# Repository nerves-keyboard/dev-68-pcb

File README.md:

# Dev-68

A 68-key development keyboard designed for working on the [Xebow](https://github.com/ElixirSeattle/xebow) firmware.

- [Bill of materials](https://docs.google.com/spreadsheets/d/1IPxDRe5p0AkolHPQgk4m-Z4O2ABlp4nutEiS4CgZYm4/edit?usp=sharing)

- [Layout](http://www.keyboard-layout-editor.com/##@@=~%0AEsc&=!%0A1&=%22%0A2&=%23%0A3&=$%0A4&=%25%0A5&=%5E%0A6&=%2F&%0A7&=*%0A8&=(%0A9&=)%0A0&=%2F_%0A-&=+%0A%2F=&_w:2%3B&=Backspace&_x:0.25%3B&=Ins&=Pg%20Up%3B&@_w:1.5%3B&=Tab&=Q&=W&=E&=R&=T&=Y&=U&=I&=O&=P&=%7B%0A%5B&=%7D%0A%5D&_w:1.5%3B&=%7C%0A%5C&_x:0.25%3B&=Del&=Pg%20Dn%3B&@_w:1.75%3B&=Caps%20Lock&=A&=S&=D&=F&=G&=H&=J&=K&=L&=%2F:%0A%2F%3B&=%22%0A'&_w:2.25%3B&=Enter%3B&@_w:2.25%3B&=Shift&=Z&=X&=C&=V&=B&=N&=M&=%3C%0A,&=%3E%0A.&=%3F%0A%2F%2F&_w:2.75%3B&=Shift&_x:0.25%3B&=%E2%86%91%3B&@_w:1.25%3B&=Ctrl&_w:1.25%3B&=Super&_w:1.25%3B&=Alt&_w:6.25%3B&=&_w:1.25%3B&=Fn&_w:1.25%3B&=Alt&_w:1.25%3B&=Ctrl&_x:0.5%3B&=%E2%86%90&=%E2%86%93&=%E2%86%92)

- PCB

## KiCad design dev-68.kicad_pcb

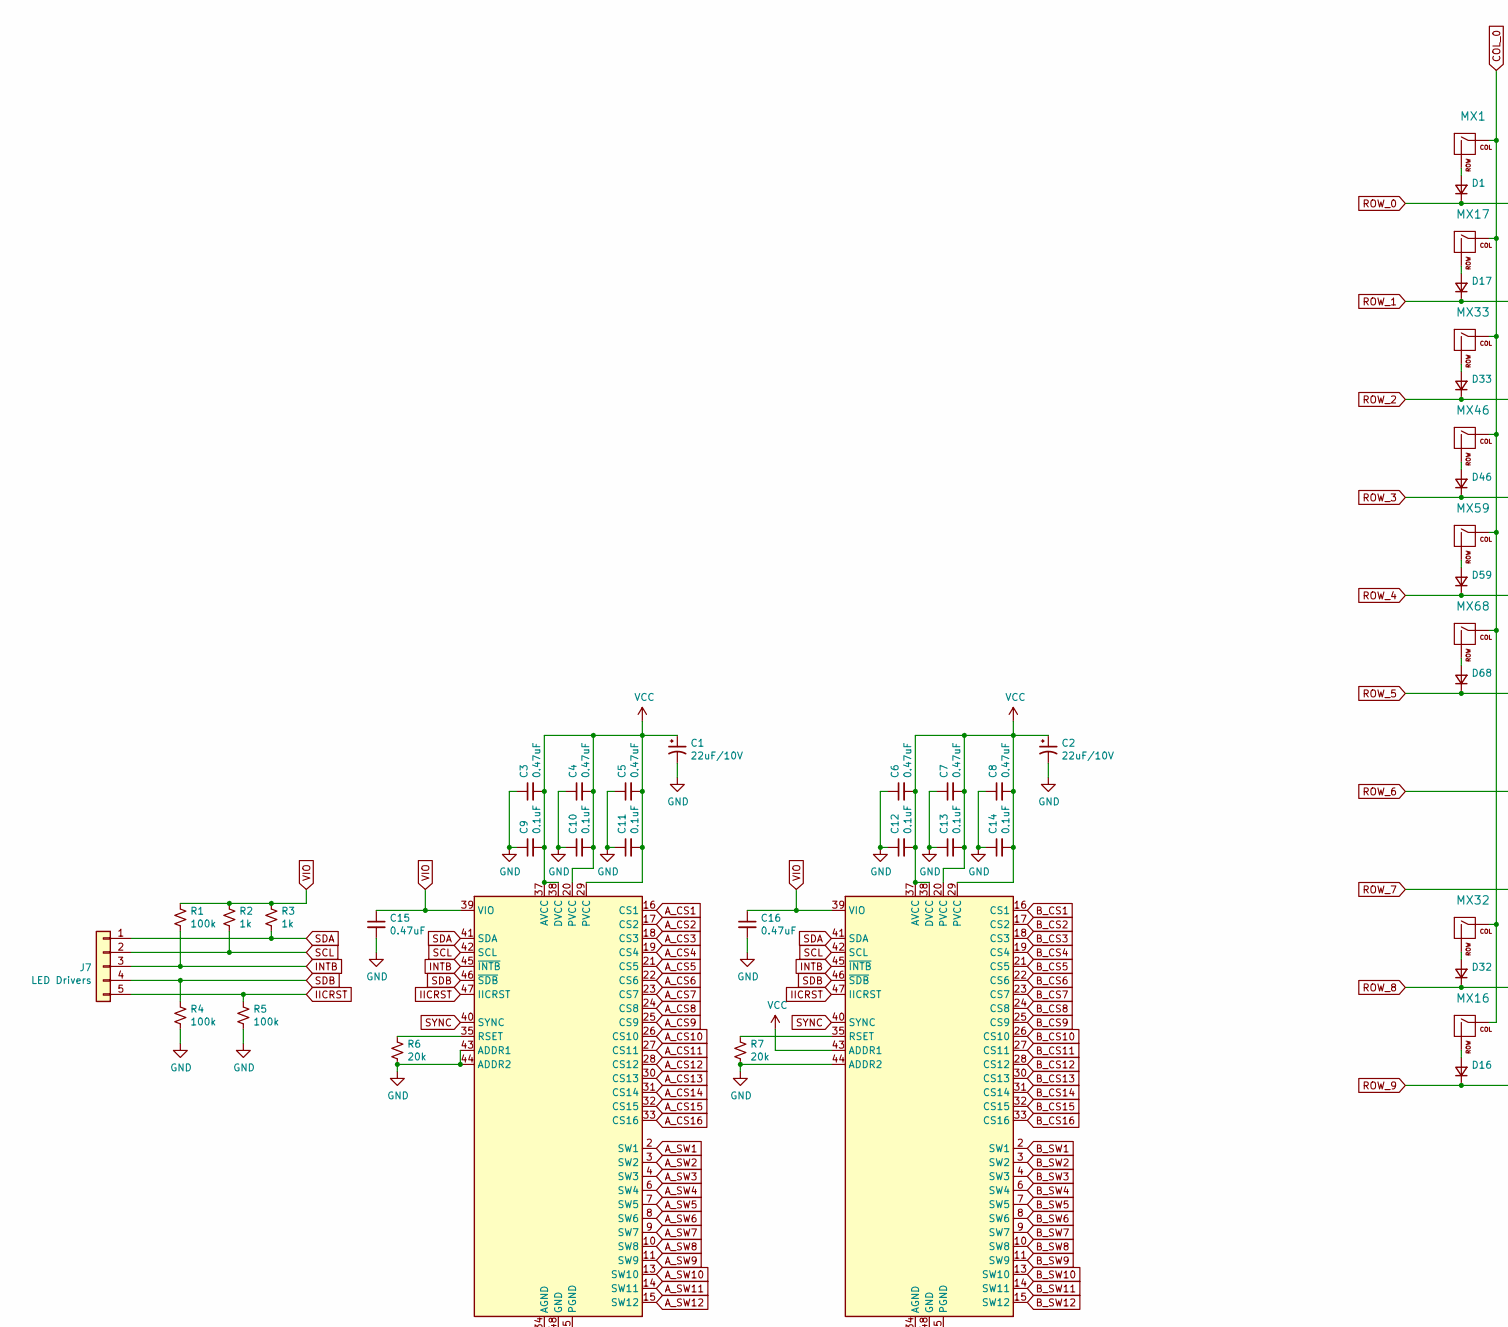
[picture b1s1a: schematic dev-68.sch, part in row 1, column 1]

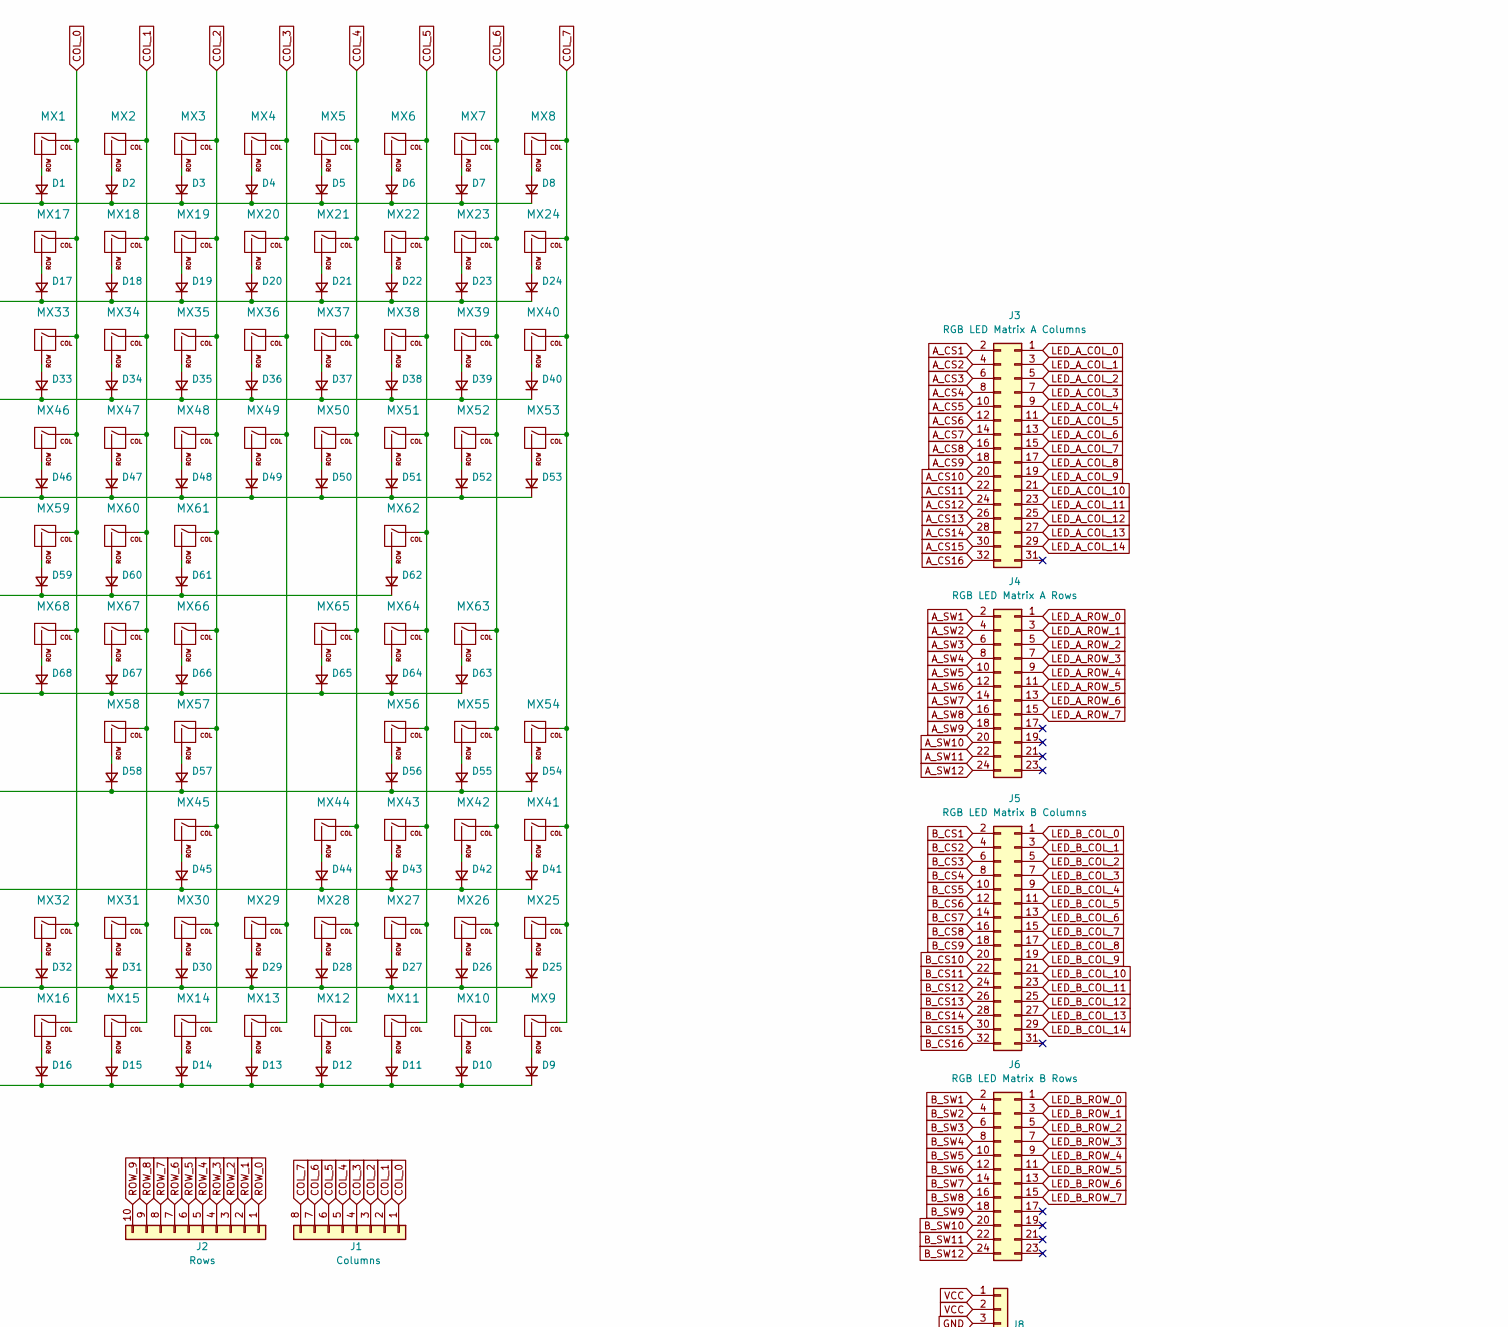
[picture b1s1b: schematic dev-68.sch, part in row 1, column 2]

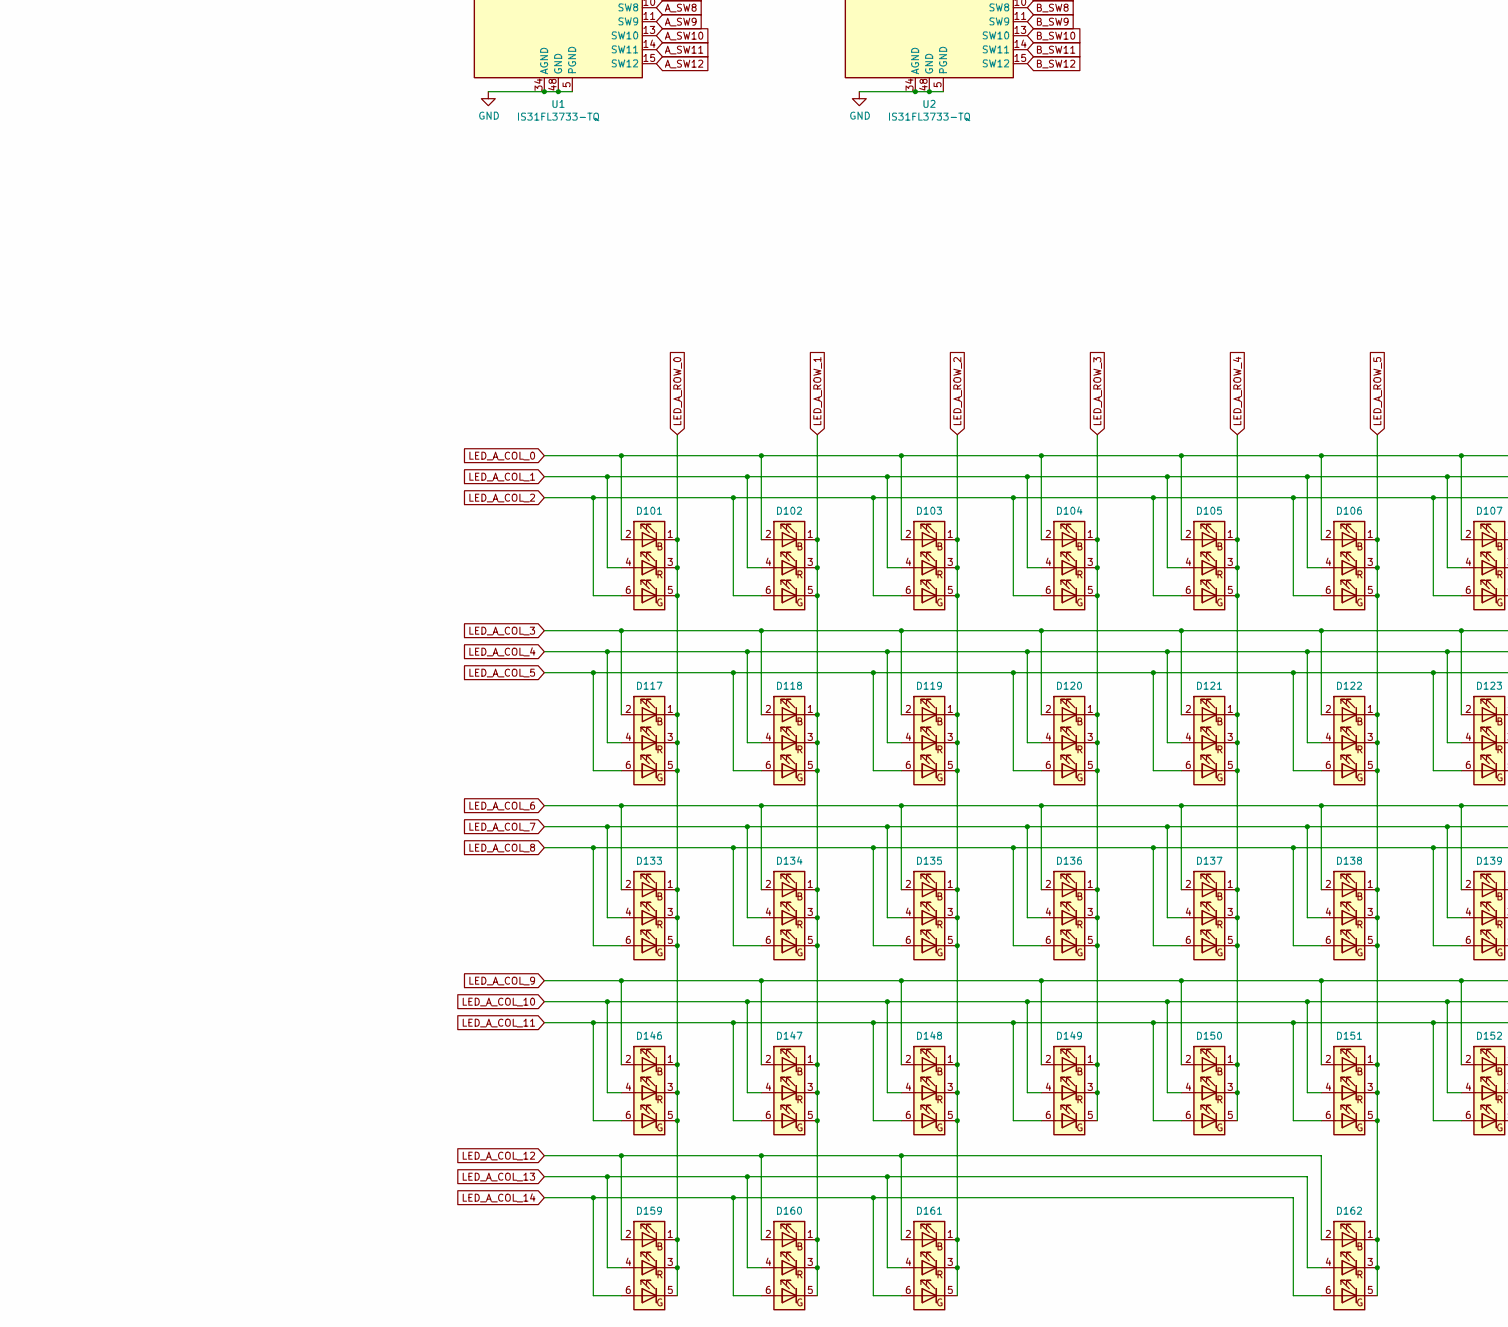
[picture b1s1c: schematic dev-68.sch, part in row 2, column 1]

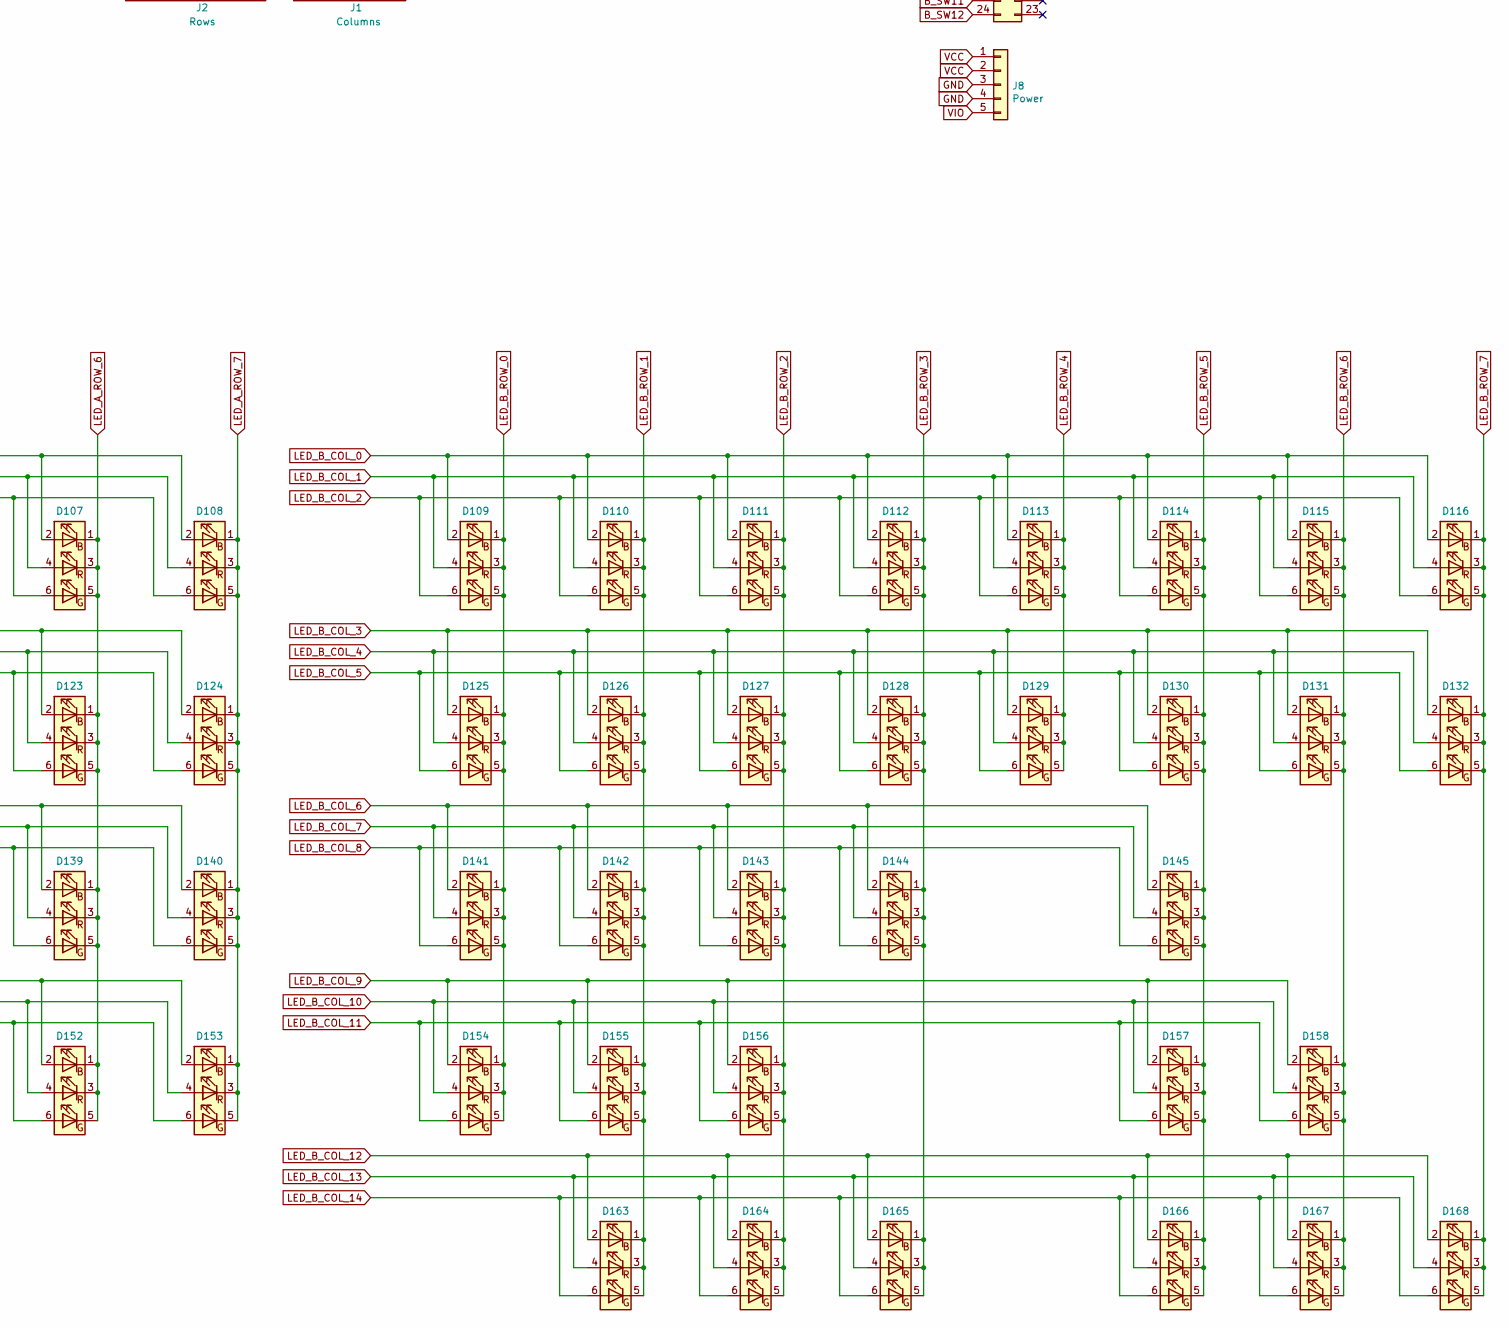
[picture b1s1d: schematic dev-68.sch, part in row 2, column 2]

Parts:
C1, C2: 22uF/10V; CP_Radial_D4.0mm_P1.50mm
C3, C4, C5, C6, C7, C8, C15, C16: 0.47uF; C_1206_3216Metric_Pad1.42x1.75mm_HandSolder
C9, C10, C11, C12, C13, C14: 0.1uF; C_1206_3216Metric_Pad1.42x1.75mm_HandSolder
D1, D2, D3, D4, D5, D6, D7, D8, D9, D10, D11, D12, D13, D14, D15, D16, D17, D18, D19, D20, D21, D22, D23, D24, D25, D26, D27, D28, D29, D30, D31, D32, D33, D34, D35, D36, D37, D38, D39, D40, D41, D42, D43, D44, D45, D46, D47, D48, D49, D50, D51, D52, D53, D54, D55, D56, D57, D58, D59, D60, D61, D62, D63, D64, D65, D66, D67, D68: D_small; D_1206_3216Metric_Pad1.42x1.75mm_HandSolder
D101, D102, D103, D104, D105, D106, D107, D108, D109, D110, D111, D112, D113, D114, D115, D116, D117, D118, D119, D120, D121, D122, D123, D124, D125, D126, D127, D128, D129, D130, D131, D132, D133, D134, D135, D136, D137, D138, D139, D140, D141, D142, D143, D144, D145, D146, D147, D148, D149, D150, D151, D152, D153, D154, D155, D156, D157, D158, D159, D160, D161, D162, D163, D164, D165, D166, D167, D168: LED_RGB; Wurth_PLCC6
J1: Columns; PinHeader_1x08_P2.54mm_Vertical
J2: Rows; PinHeader_1x10_P2.54mm_Vertical
J3: RGB LED Matrix A Columns; PinHeader_2x16_P2.54mm_Vertical
J4: RGB LED Matrix A Rows; PinHeader_2x12_P2.54mm_Vertical
J5: RGB LED Matrix B Columns; PinHeader_2x16_P2.54mm_Vertical
J6: RGB LED Matrix B Rows; PinHeader_2x12_P2.54mm_Vertical
J7: LED Drivers; PinHeader_1x05_P2.54mm_Vertical
J8: Power; PinHeader_1x05_P2.54mm_Vertical
MX1, MX2, MX3, MX4, MX5, MX6, MX7, MX8, MX9, MX10, MX11, MX12, MX13, MX15, MX16, MX18, MX19, MX20, MX21, MX22, MX23, MX24, MX25, MX26, MX27, MX28, MX29, MX31, MX32, MX34, MX35, MX36, MX37, MX38, MX39, MX40, MX41, MX42, MX43, MX44, MX47, MX48, MX49, MX50, MX51, MX52, MX53, MX54, MX55, MX56, MX58, MX66, MX67, MX68: MX-NoLED; MXOnly-1U-Hotswap
MX14: MX-NoLED; MXOnly-2U-Hotswap-ReversedStabilizers
MX17, MX30: MX-NoLED; MXOnly-1.5U-Hotswap
MX33: MX-NoLED; MXOnly-1.75U-Hotswap
MX45, MX46: MX-NoLED; MXOnly-2.25U-Hotswap-ReversedStabilizers
MX57: MX-NoLED; MXOnly-2.75U-Hotswap-ReversedStabilizers
MX59, MX60, MX61, MX63, MX64, MX65: MX-NoLED; MXOnly-1.25U-Hotswap
MX62: MX-NoLED; MXOnly-6.25U-Hotswap-ReversedStabilizers
R1, R4, R5: 100k; R_1206_3216Metric_Pad1.42x1.75mm_HandSolder
R2, R3: 1k; R_1206_3216Metric_Pad1.42x1.75mm_HandSolder
R6, R7: 20k; R_1206_3216Metric_Pad1.42x1.75mm_HandSolder
U1, U2: IS31FL3733-TQ; TQFP-48-1EP_7x7mm_P0.5mm_EP5x5mm

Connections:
A_CS1: J3.2, U1.16 (CS1)
A_CS2: J3.4, U1.17 (CS2)
A_CS3: J3.6, U1.18 (CS3)
A_CS4: J3.8, U1.19 (CS4)
A_CS5: J3.10, U1.21 (CS5)
A_CS6: J3.12, U1.22 (CS6)
A_CS7: J3.14, U1.23 (CS7)
A_CS8: J3.16, U1.24 (CS8)
A_CS9: J3.18, U1.25 (CS9)
A_CS10: J3.20, U1.26 (CS10)
A_CS11: J3.22, U1.27 (CS11)
A_CS12: J3.24, U1.28 (CS12)
A_CS13: J3.26, U1.30 (CS13)
A_CS14: J3.28, U1.31 (CS14)
A_CS15: J3.30, U1.32 (CS15)
A_CS16: J3.32, U1.33 (CS16)
A_SW1: J4.2, U1.2 (SW1)
A_SW2: J4.4, U1.3 (SW2)
A_SW3: J4.6, U1.4 (SW3)
A_SW4: J4.8, U1.6 (SW4)
A_SW5: J4.10, U1.7 (SW5)
A_SW6: J4.12, U1.8 (SW6)
A_SW7: J4.14, U1.9 (SW7)
A_SW8: J4.16, U1.10 (SW8)
A_SW9: J4.18, U1.11 (SW9)
A_SW10: J4.20, U1.13 (SW10)
A_SW11: J4.22, U1.14 (SW11)
A_SW12: J4.24, U1.15 (SW12)
B_CS1: J5.2, U2.16 (CS1)
B_CS2: J5.4, U2.17 (CS2)
B_CS3: J5.6, U2.18 (CS3)
B_CS4: J5.8, U2.19 (CS4)
B_CS5: J5.10, U2.21 (CS5)
B_CS6: J5.12, U2.22 (CS6)
B_CS7: J5.14, U2.23 (CS7)
B_CS8: J5.16, U2.24 (CS8)
B_CS9: J5.18, U2.25 (CS9)
B_CS10: J5.20, U2.26 (CS10)
B_CS11: J5.22, U2.27 (CS11)
B_CS12: J5.24, U2.28 (CS12)
B_CS13: J5.26, U2.30 (CS13)
B_CS14: J5.28, U2.31 (CS14)
B_CS15: J5.30, U2.32 (CS15)
B_CS16: J5.32, U2.33 (CS16)
B_SW1: J6.2, U2.2 (SW1)
B_SW2: J6.4, U2.3 (SW2)
B_SW3: J6.6, U2.4 (SW3)
B_SW4: J6.8, U2.6 (SW4)
B_SW5: J6.10, U2.7 (SW5)
B_SW6: J6.12, U2.8 (SW6)
B_SW7: J6.14, U2.9 (SW7)
B_SW8: J6.16, U2.10 (SW8)
B_SW9: J6.18, U2.11 (SW9)
B_SW10: J6.20, U2.13 (SW10)
B_SW11: J6.22, U2.14 (SW11)
B_SW12: J6.24, U2.15 (SW12)
COL_0: J1.1, MX1.1 (COL), MX16.1 (COL), MX17.1 (COL), MX32.1 (COL), MX33.1 (COL), MX46.1 (COL), MX59.1 (COL), MX68.1 (COL)
COL_1: J1.2, MX2.1 (COL), MX15.1 (COL), MX18.1 (COL), MX31.1 (COL), MX34.1 (COL), MX47.1 (COL), MX58.1 (COL), MX60.1 (COL), MX67.1 (COL)
COL_2: J1.3, MX3.1 (COL), MX14.1 (COL), MX19.1 (COL), MX30.1 (COL), MX35.1 (COL), MX45.1 (COL), MX48.1 (COL), MX57.1 (COL), MX61.1 (COL), MX66.1 (COL)
COL_3: J1.4, MX4.1 (COL), MX13.1 (COL), MX20.1 (COL), MX29.1 (COL), MX36.1 (COL), MX49.1 (COL)
COL_4: J1.5, MX5.1 (COL), MX12.1 (COL), MX21.1 (COL), MX28.1 (COL), MX37.1 (COL), MX44.1 (COL), MX50.1 (COL), MX65.1 (COL)
COL_5: J1.6, MX6.1 (COL), MX11.1 (COL), MX22.1 (COL), MX27.1 (COL), MX38.1 (COL), MX43.1 (COL), MX51.1 (COL), MX56.1 (COL), MX62.1 (COL), MX64.1 (COL)
COL_6: J1.7, MX7.1 (COL), MX10.1 (COL), MX23.1 (COL), MX26.1 (COL), MX39.1 (COL), MX42.1 (COL), MX52.1 (COL), MX55.1 (COL), MX63.1 (COL)
COL_7: J1.8, MX8.1 (COL), MX9.1 (COL), MX24.1 (COL), MX25.1 (COL), MX40.1 (COL), MX41.1 (COL), MX53.1 (COL), MX54.1 (COL)
GND: C1.2, C2.2, C3.1, C4.1, C5.1, C6.1, C7.1, C8.1, C9.1, C10.1, C11.1, C12.1, C13.1, C14.1, C15.2, C16.2, J8.3, J8.4, R4.2, R5.2, R6.2, R7.2, U1.5 (PGND), U1.12 (PGND), U1.34 (AGND), U1.43 (ADDR1), U1.44 (ADDR2), U1.48 (GND), U1.49 (GND), U2.5 (PGND), U2.12 (PGND), U2.34 (AGND), U2.44 (ADDR2), U2.48 (GND), U2.49 (GND)
IICRST: J7.5, R5.1, U1.47 (IICRST), U2.47 (IICRST)
INTB: J7.3, R1.2, U1.45 (~INTB), U2.45 (~INTB)
LED_A_COL_0: D101.2 (BA), D102.2 (BA), D103.2 (BA), D104.2 (BA), D105.2 (BA), D106.2 (BA), D107.2 (BA), D108.2 (BA), J3.1
LED_A_COL_1: D101.4 (RA), D102.4 (RA), D103.4 (RA), D104.4 (RA), D105.4 (RA), D106.4 (RA), D107.4 (RA), D108.4 (RA), J3.3
LED_A_COL_2: D101.6 (GA), D102.6 (GA), D103.6 (GA), D104.6 (GA), D105.6 (GA), D106.6 (GA), D107.6 (GA), D108.6 (GA), J3.5
LED_A_COL_3: D117.2 (BA), D118.2 (BA), D119.2 (BA), D120.2 (BA), D121.2 (BA), D122.2 (BA), D123.2 (BA), D124.2 (BA), J3.7
LED_A_COL_4: D117.4 (RA), D118.4 (RA), D119.4 (RA), D120.4 (RA), D121.4 (RA), D122.4 (RA), D123.4 (RA), D124.4 (RA), J3.9
LED_A_COL_5: D117.6 (GA), D118.6 (GA), D119.6 (GA), D120.6 (GA), D121.6 (GA), D122.6 (GA), D123.6 (GA), D124.6 (GA), J3.11
LED_A_COL_6: D133.2 (BA), D134.2 (BA), D135.2 (BA), D136.2 (BA), D137.2 (BA), D138.2 (BA), D139.2 (BA), D140.2 (BA), J3.13
LED_A_COL_7: D133.4 (RA), D134.4 (RA), D135.4 (RA), D136.4 (RA), D137.4 (RA), D138.4 (RA), D139.4 (RA), D140.4 (RA), J3.15
LED_A_COL_8: D133.6 (GA), D134.6 (GA), D135.6 (GA), D136.6 (GA), D137.6 (GA), D138.6 (GA), D139.6 (GA), D140.6 (GA), J3.17
LED_A_COL_9: D146.2 (BA), D147.2 (BA), D148.2 (BA), D149.2 (BA), D150.2 (BA), D151.2 (BA), D152.2 (BA), D153.2 (BA), J3.19
LED_A_COL_10: D146.4 (RA), D147.4 (RA), D148.4 (RA), D149.4 (RA), D150.4 (RA), D151.4 (RA), D152.4 (RA), D153.4 (RA), J3.21
LED_A_COL_11: D146.6 (GA), D147.6 (GA), D148.6 (GA), D149.6 (GA), D150.6 (GA), D151.6 (GA), D152.6 (GA), D153.6 (GA), J3.23
LED_A_COL_12: D159.2 (BA), D160.2 (BA), D161.2 (BA), D162.2 (BA), J3.25
LED_A_COL_13: D159.4 (RA), D160.4 (RA), D161.4 (RA), D162.4 (RA), J3.27
LED_A_COL_14: D159.6 (GA), D160.6 (GA), D161.6 (GA), D162.6 (GA), J3.29
LED_A_ROW_0: D101.1 (BK), D101.3 (RK), D101.5 (GK), D117.1 (BK), D117.3 (RK), D117.5 (GK), D133.1 (BK), D133.3 (RK), D133.5 (GK), D146.1 (BK), D146.3 (RK), D146.5 (GK), D159.1 (BK), D159.3 (RK), D159.5 (GK), J4.1
LED_A_ROW_1: D102.1 (BK), D102.3 (RK), D102.5 (GK), D118.1 (BK), D118.3 (RK), D118.5 (GK), D134.1 (BK), D134.3 (RK), D134.5 (GK), D147.1 (BK), D147.3 (RK), D147.5 (GK), D160.1 (BK), D160.3 (RK), D160.5 (GK), J4.3
LED_A_ROW_2: D103.1 (BK), D103.3 (RK), D103.5 (GK), D119.1 (BK), D119.3 (RK), D119.5 (GK), D135.1 (BK), D135.3 (RK), D135.5 (GK), D148.1 (BK), D148.3 (RK), D148.5 (GK), D161.1 (BK), D161.3 (RK), D161.5 (GK), J4.5
LED_A_ROW_3: D104.1 (BK), D104.3 (RK), D104.5 (GK), D120.1 (BK), D120.3 (RK), D120.5 (GK), D136.1 (BK), D136.3 (RK), D136.5 (GK), D149.1 (BK), D149.3 (RK), D149.5 (GK), J4.7
LED_A_ROW_4: D105.1 (BK), D105.3 (RK), D105.5 (GK), D121.1 (BK), D121.3 (RK), D121.5 (GK), D137.1 (BK), D137.3 (RK), D137.5 (GK), D150.1 (BK), D150.3 (RK), D150.5 (GK), J4.9
LED_A_ROW_5: D106.1 (BK), D106.3 (RK), D106.5 (GK), D122.1 (BK), D122.3 (RK), D122.5 (GK), D138.1 (BK), D138.3 (RK), D138.5 (GK), D151.1 (BK), D151.3 (RK), D151.5 (GK), D162.1 (BK), D162.3 (RK), D162.5 (GK), J4.11
LED_A_ROW_6: D107.1 (BK), D107.3 (RK), D107.5 (GK), D123.1 (BK), D123.3 (RK), D123.5 (GK), D139.1 (BK), D139.3 (RK), D139.5 (GK), D152.1 (BK), D152.3 (RK), D152.5 (GK), J4.13
LED_A_ROW_7: D108.1 (BK), D108.3 (RK), D108.5 (GK), D124.1 (BK), D124.3 (RK), D124.5 (GK), D140.1 (BK), D140.3 (RK), D140.5 (GK), D153.1 (BK), D153.3 (RK), D153.5 (GK), J4.15
LED_B_COL_0: D109.2 (BA), D110.2 (BA), D111.2 (BA), D112.2 (BA), D113.2 (BA), D114.2 (BA), D115.2 (BA), D116.2 (BA), J5.1
LED_B_COL_1: D109.4 (RA), D110.4 (RA), D111.4 (RA), D112.4 (RA), D113.4 (RA), D114.4 (RA), D115.4 (RA), D116.4 (RA), J5.3
LED_B_COL_2: D109.6 (GA), D110.6 (GA), D111.6 (GA), D112.6 (GA), D113.6 (GA), D114.6 (GA), D115.6 (GA), D116.6 (GA), J5.5
LED_B_COL_3: D125.2 (BA), D126.2 (BA), D127.2 (BA), D128.2 (BA), D129.2 (BA), D130.2 (BA), D131.2 (BA), D132.2 (BA), J5.7
LED_B_COL_4: D125.4 (RA), D126.4 (RA), D127.4 (RA), D128.4 (RA), D129.4 (RA), D130.4 (RA), D131.4 (RA), D132.4 (RA), J5.9
LED_B_COL_5: D125.6 (GA), D126.6 (GA), D127.6 (GA), D128.6 (GA), D129.6 (GA), D130.6 (GA), D131.6 (GA), D132.6 (GA), J5.11
LED_B_COL_6: D141.2 (BA), D142.2 (BA), D143.2 (BA), D144.2 (BA), D145.2 (BA), J5.13
LED_B_COL_7: D141.4 (RA), D142.4 (RA), D143.4 (RA), D144.4 (RA), D145.4 (RA), J5.15
LED_B_COL_8: D141.6 (GA), D142.6 (GA), D143.6 (GA), D144.6 (GA), D145.6 (GA), J5.17
LED_B_COL_9: D154.2 (BA), D155.2 (BA), D156.2 (BA), D157.2 (BA), D158.2 (BA), J5.19
LED_B_COL_10: D154.4 (RA), D155.4 (RA), D156.4 (RA), D157.4 (RA), D158.4 (RA), J5.21
LED_B_COL_11: D154.6 (GA), D155.6 (GA), D156.6 (GA), D157.6 (GA), D158.6 (GA), J5.23
LED_B_COL_12: D163.2 (BA), D164.2 (BA), D165.2 (BA), D166.2 (BA), D167.2 (BA), D168.2 (BA), J5.25
LED_B_COL_13: D163.4 (RA), D164.4 (RA), D165.4 (RA), D166.4 (RA), D167.4 (RA), D168.4 (RA), J5.27
LED_B_COL_14: D163.6 (GA), D164.6 (GA), D165.6 (GA), D166.6 (GA), D167.6 (GA), D168.6 (GA), J5.29
LED_B_ROW_0: D109.1 (BK), D109.3 (RK), D109.5 (GK), D125.1 (BK), D125.3 (RK), D125.5 (GK), D141.1 (BK), D141.3 (RK), D141.5 (GK), D154.1 (BK), D154.3 (RK), D154.5 (GK), J6.1
LED_B_ROW_1: D110.1 (BK), D110.3 (RK), D110.5 (GK), D126.1 (BK), D126.3 (RK), D126.5 (GK), D142.1 (BK), D142.3 (RK), D142.5 (GK), D155.1 (BK), D155.3 (RK), D155.5 (GK), D163.1 (BK), D163.3 (RK), D163.5 (GK), J6.3
LED_B_ROW_2: D111.1 (BK), D111.3 (RK), D111.5 (GK), D127.1 (BK), D127.3 (RK), D127.5 (GK), D143.1 (BK), D143.3 (RK), D143.5 (GK), D156.1 (BK), D156.3 (RK), D156.5 (GK), D164.1 (BK), D164.3 (RK), D164.5 (GK), J6.5
LED_B_ROW_3: D112.1 (BK), D112.3 (RK), D112.5 (GK), D128.1 (BK), D128.3 (RK), D128.5 (GK), D144.1 (BK), D144.3 (RK), D144.5 (GK), D165.1 (BK), D165.3 (RK), D165.5 (GK), J6.7
LED_B_ROW_4: D113.1 (BK), D113.3 (RK), D113.5 (GK), D129.1 (BK), D129.3 (RK), D129.5 (GK), J6.9
LED_B_ROW_5: D114.1 (BK), D114.3 (RK), D114.5 (GK), D130.1 (BK), D130.3 (RK), D130.5 (GK), D145.1 (BK), D145.3 (RK), D145.5 (GK), D157.1 (BK), D157.3 (RK), D157.5 (GK), D166.1 (BK), D166.3 (RK), D166.5 (GK), J6.11
LED_B_ROW_6: D115.1 (BK), D115.3 (RK), D115.5 (GK), D131.1 (BK), D131.3 (RK), D131.5 (GK), D158.1 (BK), D158.3 (RK), D158.5 (GK), D167.1 (BK), D167.3 (RK), D167.5 (GK), J6.13
LED_B_ROW_7: D116.1 (BK), D116.3 (RK), D116.5 (GK), D132.1 (BK), D132.3 (RK), D132.5 (GK), D168.1 (BK), D168.3 (RK), D168.5 (GK), J6.15
unnamed: D1.2 (A), MX1.2 (ROW)
unnamed: D2.2 (A), MX2.2 (ROW)
unnamed: D3.2 (A), MX3.2 (ROW)
unnamed: D4.2 (A), MX4.2 (ROW)
unnamed: D5.2 (A), MX5.2 (ROW)
unnamed: D6.2 (A), MX6.2 (ROW)
unnamed: D7.2 (A), MX7.2 (ROW)
unnamed: D8.2 (A), MX8.2 (ROW)
unnamed: D9.2 (A), MX9.2 (ROW)
unnamed: D10.2 (A), MX10.2 (ROW)
unnamed: D11.2 (A), MX11.2 (ROW)
unnamed: D12.2 (A), MX12.2 (ROW)
unnamed: D13.2 (A), MX13.2 (ROW)
unnamed: D14.2 (A), MX14.2 (ROW)
unnamed: D15.2 (A), MX15.2 (ROW)
unnamed: D16.2 (A), MX16.2 (ROW)
unnamed: D17.2 (A), MX17.2 (ROW)
unnamed: D18.2 (A), MX18.2 (ROW)
unnamed: D19.2 (A), MX19.2 (ROW)
unnamed: D20.2 (A), MX20.2 (ROW)
unnamed: D21.2 (A), MX21.2 (ROW)
unnamed: D22.2 (A), MX22.2 (ROW)
unnamed: D23.2 (A), MX23.2 (ROW)
unnamed: D24.2 (A), MX24.2 (ROW)
unnamed: D25.2 (A), MX25.2 (ROW)
unnamed: D26.2 (A), MX26.2 (ROW)
unnamed: D27.2 (A), MX27.2 (ROW)
unnamed: D28.2 (A), MX28.2 (ROW)
unnamed: D29.2 (A), MX29.2 (ROW)
unnamed: D30.2 (A), MX30.2 (ROW)
unnamed: D31.2 (A), MX31.2 (ROW)
unnamed: D32.2 (A), MX32.2 (ROW)
unnamed: D33.2 (A), MX33.2 (ROW)
unnamed: D34.2 (A), MX34.2 (ROW)
unnamed: D35.2 (A), MX35.2 (ROW)
unnamed: D36.2 (A), MX36.2 (ROW)
unnamed: D37.2 (A), MX37.2 (ROW)
unnamed: D38.2 (A), MX38.2 (ROW)
unnamed: D39.2 (A), MX39.2 (ROW)
unnamed: D40.2 (A), MX40.2 (ROW)
unnamed: D41.2 (A), MX41.2 (ROW)
unnamed: D42.2 (A), MX42.2 (ROW)
unnamed: D43.2 (A), MX43.2 (ROW)
unnamed: D44.2 (A), MX44.2 (ROW)
unnamed: D45.2 (A), MX45.2 (ROW)
unnamed: D46.2 (A), MX46.2 (ROW)
unnamed: D47.2 (A), MX47.2 (ROW)
unnamed: D48.2 (A), MX48.2 (ROW)
unnamed: D49.2 (A), MX49.2 (ROW)
unnamed: D50.2 (A), MX50.2 (ROW)
unnamed: D51.2 (A), MX51.2 (ROW)
unnamed: D52.2 (A), MX52.2 (ROW)
unnamed: D53.2 (A), MX53.2 (ROW)
unnamed: D54.2 (A), MX54.2 (ROW)
unnamed: D55.2 (A), MX55.2 (ROW)
unnamed: D56.2 (A), MX56.2 (ROW)
unnamed: D57.2 (A), MX57.2 (ROW)
unnamed: D58.2 (A), MX58.2 (ROW)
unnamed: D59.2 (A), MX59.2 (ROW)
unnamed: D60.2 (A), MX60.2 (ROW)
unnamed: D61.2 (A), MX61.2 (ROW)
unnamed: D62.2 (A), MX62.2 (ROW)
unnamed: D63.2 (A), MX63.2 (ROW)
unnamed: D64.2 (A), MX64.2 (ROW)
unnamed: D65.2 (A), MX65.2 (ROW)
unnamed: D66.2 (A), MX66.2 (ROW)
unnamed: D67.2 (A), MX67.2 (ROW)
unnamed: D68.2 (A), MX68.2 (ROW)
unnamed: R6.1, U1.35 (RSET)
unnamed: R7.1, U2.35 (RSET)
ROW_0: D1.1 (K), D2.1 (K), D3.1 (K), D4.1 (K), D5.1 (K), D6.1 (K), D7.1 (K), D8.1 (K), J2.1
ROW_1: D17.1 (K), D18.1 (K), D19.1 (K), D20.1 (K), D21.1 (K), D22.1 (K), D23.1 (K), D24.1 (K), J2.2
ROW_2: D33.1 (K), D34.1 (K), D35.1 (K), D36.1 (K), D37.1 (K), D38.1 (K), D39.1 (K), D40.1 (K), J2.3
ROW_3: D46.1 (K), D47.1 (K), D48.1 (K), D49.1 (K), D50.1 (K), D51.1 (K), D52.1 (K), D53.1 (K), J2.4
ROW_4: D59.1 (K), D60.1 (K), D61.1 (K), D62.1 (K), J2.5
ROW_5: D63.1 (K), D64.1 (K), D65.1 (K), D66.1 (K), D67.1 (K), D68.1 (K), J2.6
ROW_6: D54.1 (K), D55.1 (K), D56.1 (K), D57.1 (K), D58.1 (K), J2.7
ROW_7: D41.1 (K), D42.1 (K), D43.1 (K), D44.1 (K), D45.1 (K), J2.8
ROW_8: D25.1 (K), D26.1 (K), D27.1 (K), D28.1 (K), D29.1 (K), D30.1 (K), D31.1 (K), D32.1 (K), J2.9
ROW_9: D9.1 (K), D10.1 (K), D11.1 (K), D12.1 (K), D13.1 (K), D14.1 (K), D15.1 (K), D16.1 (K), J2.10
SCL: J7.2, R2.2, U1.42 (SCL), U2.42 (SCL)
SDA: J7.1, R3.2, U1.41 (SDA), U2.41 (SDA)
SDB: J7.4, R4.1, U1.46 (~SDB), U2.46 (~SDB)
SYNC: U1.40 (SYNC), U2.40 (SYNC)
VCC: C1.1, C2.1, C3.2, C4.2, C5.2, C6.2, C7.2, C8.2, C9.2, C10.2, C11.2, C12.2, C13.2, C14.2, J8.1, J8.2, U1.20 (PVCC), U1.29 (PVCC), U1.37 (AVCC), U1.38 (DVCC), U2.20 (PVCC), U2.29 (PVCC), U2.37 (AVCC), U2.38 (DVCC), U2.43 (ADDR1)
VIO: C15.1, C16.1, J8.5, R1.1, R2.1, R3.1, U1.39 (VIO), U2.39 (VIO)

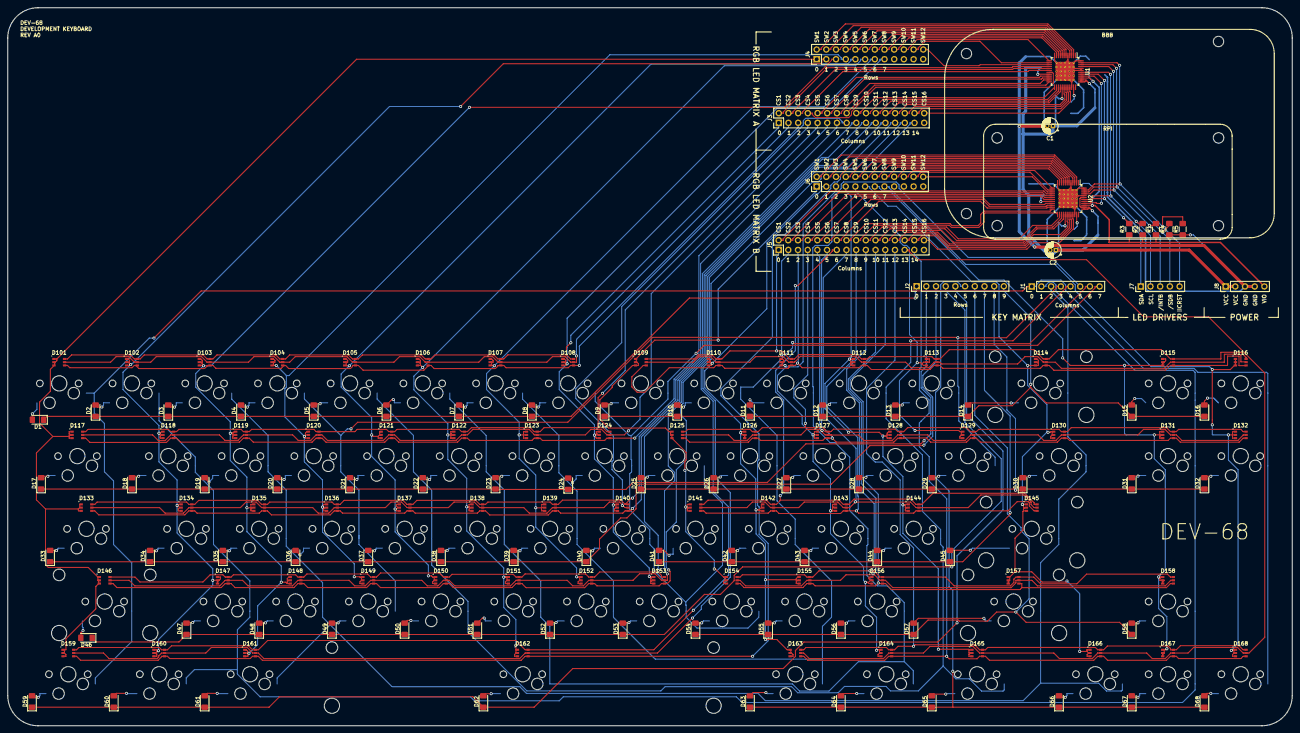
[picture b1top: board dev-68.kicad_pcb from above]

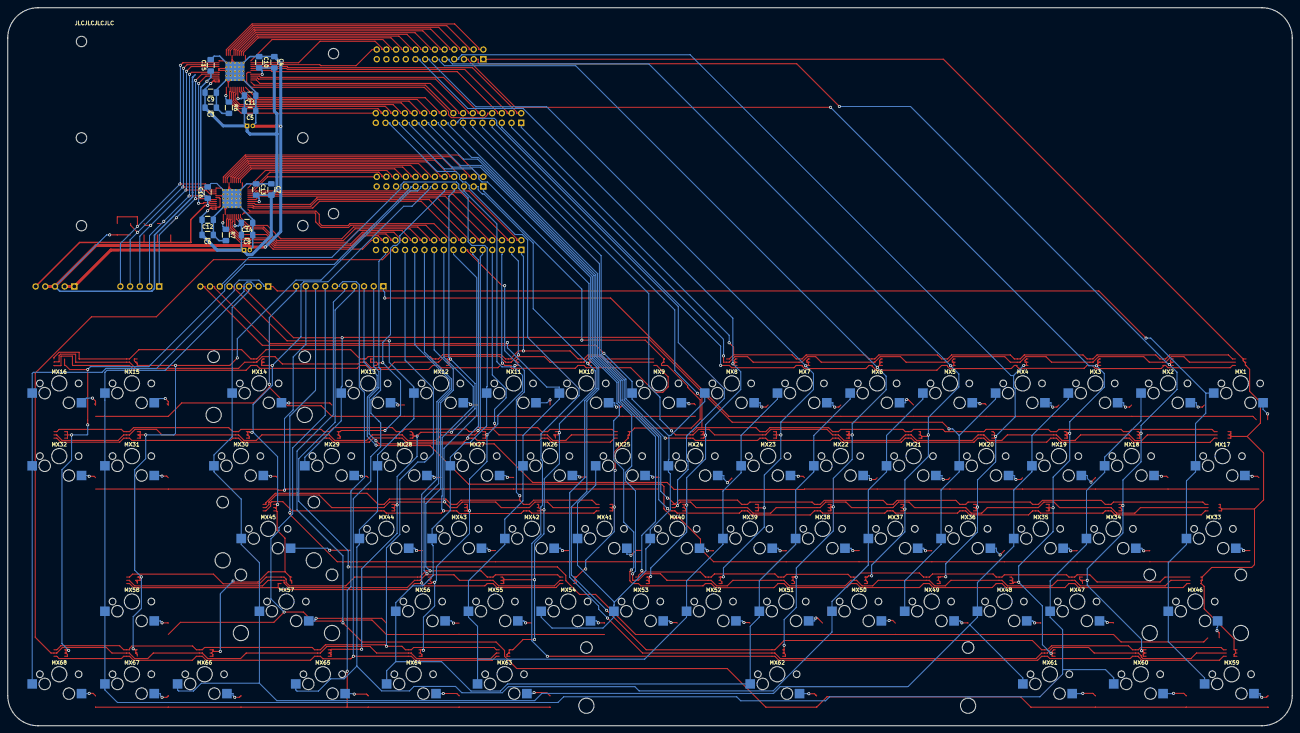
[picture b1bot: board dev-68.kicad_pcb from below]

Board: 2 copper layers, 336.6 x 188.1 mm, 238 parts (16 on the bottom side), 199 nets.

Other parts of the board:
J9: RPI; Raspberry_Pi_Zero_Socketed_THT_FaceDown_MountingHoles

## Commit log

2020-08-19 Better columns
2020-08-19 Initial import.
2020-08-19 Setup .gitignore for KiCad.
2020-08-19 Rename project to dev-68.
2020-08-19 Add BBB footprint to project library.
2020-08-23 Change library paths to relative.
2020-08-24 RGB LEDs and project rename
2020-08-24 Some tracing
2020-08-24 Undo some traces; do just the "easy" traces.
2020-08-24 Minimized vias
2020-08-24 RGB LED traces
2020-08-24 so. many. traces...
2020-08-24 LED A Matrix + Rows and Cols
2020-08-25 Finished traces
2020-08-25 cleanup
2020-08-26 Better placement
2020-08-29 Update schematic with all required 3733 components
2020-08-29 Footprints for 3733 components
2020-08-29 some driver tracing
2020-08-29 Finished drivver area routing
2020-08-30 Final? revisions
2020-08-31 Fix silkscreen labels
2020-08-31 Small fixes
2020-08-31 Remove session
2020-08-31 Remove more unused files
2020-08-31 Rounded edges
2020-08-31 Fix exposed traces
2020-08-31 Add gitignore
2020-08-31 Add readme.
2020-08-31 Add board renders to README
2020-09-01 Update .gitignore.
2020-09-01 Disconnect one side of GND guarding I2C bus. Clean up C1 & C2 traces.
2020-09-01 Don't track backup file.
2020-09-01 Fix DRC errors.
2020-09-01 Add JLCPCB order number marker.
2020-09-01 Don't track cache file.
2020-09-02 Ignore output directory.
2020-09-03 Add keys 15 and 16 back on PCB.
2020-09-03 Fix BBB silk screen outline.
2022-07-23 Add link to bill of materials.
